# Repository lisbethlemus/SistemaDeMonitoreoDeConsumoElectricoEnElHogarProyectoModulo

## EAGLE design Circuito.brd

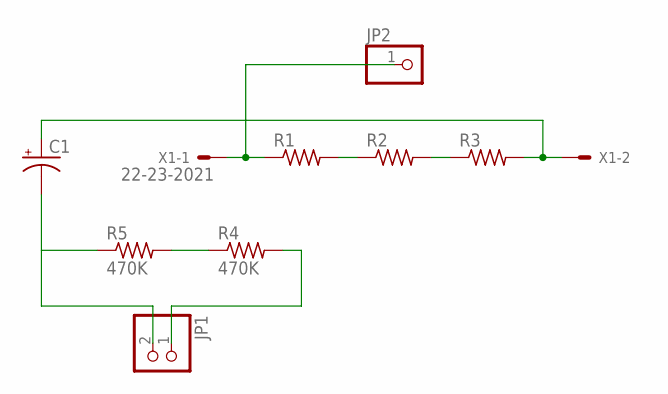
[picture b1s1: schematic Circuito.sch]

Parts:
C1: CPOL-USE2.5-7; E2,5-7
JP1: PINHD-1X2; 1X02
JP2: PINHD-1X1; 1X01
R1, R2, R3: R-US_0204/7; 0204/7
R4, R5: 470K; 0204/7
X1: 22-23-2021

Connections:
unnamed: C1.-, JP1.2, R5.1
unnamed: R4.1, R5.2
unnamed: R1.2, R2.1
unnamed: R2.2, R3.1
unnamed: JP2.1, R1.1, X1.1
unnamed: C1.+, R3.2, X1.2
unnamed: JP1.1, R4.2

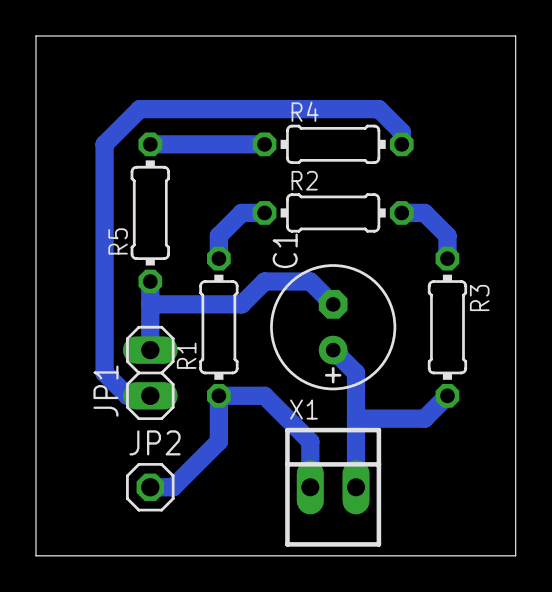
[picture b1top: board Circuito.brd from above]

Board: 2 copper layers, 26.7 x 28.9 mm, 9 parts (0 on the bottom side), 7 nets.
